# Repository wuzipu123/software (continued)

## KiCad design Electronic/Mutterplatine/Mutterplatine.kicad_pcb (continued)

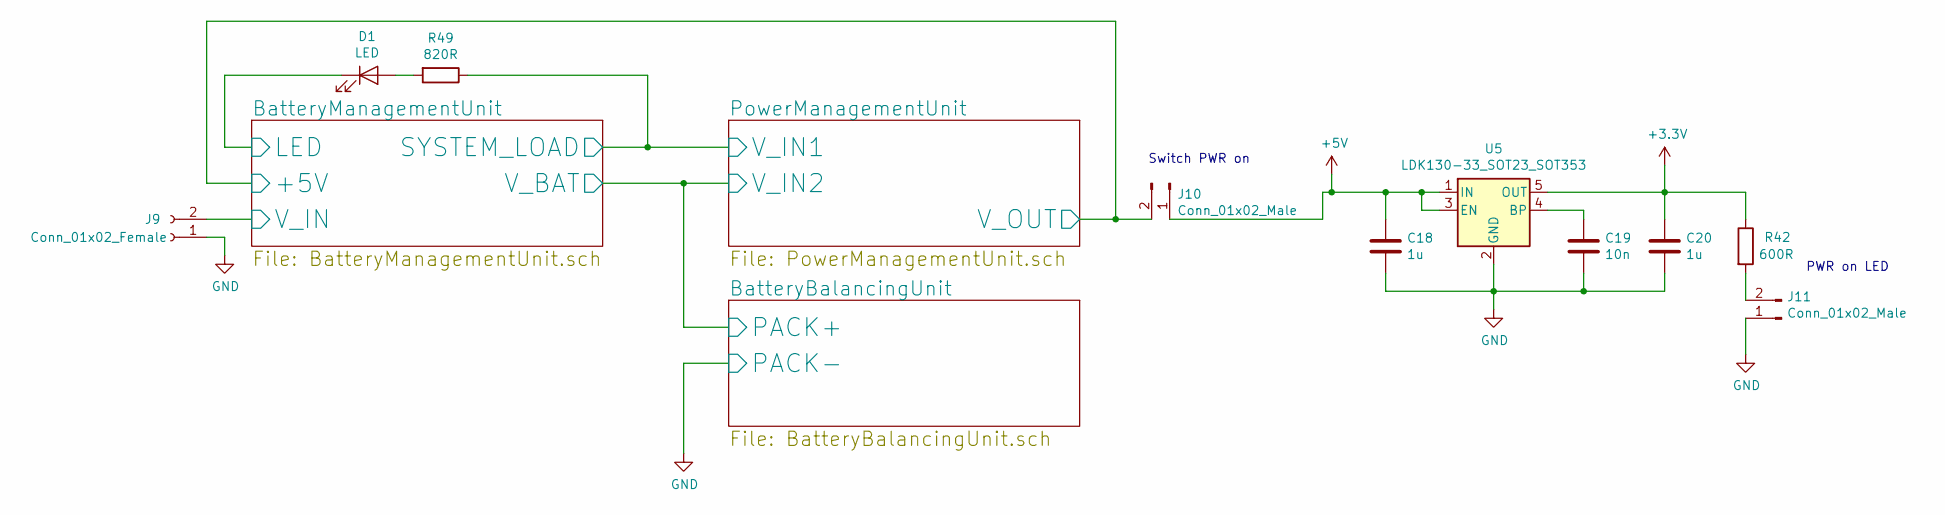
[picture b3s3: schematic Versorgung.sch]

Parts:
C18, C20: 1u; C_0805_2012Metric_Pad1.15x1.40mm_HandSolder
C19: 10n; C_0805_2012Metric_Pad1.15x1.40mm_HandSolder
D1: LED; Pin_Header_Straight_1x02_Pitch2.54mm
J9: Conn_01x02_Female; PhoenixContact_MCV-G_02x5.08mm_Vertical
J10, J11: Conn_01x02_Male; PinHeader_1x02_P2.54mm_Vertical
R42: 600R; R_0805_2012Metric_Pad1.15x1.40mm_HandSolder
R49: 820R; R_0805
U5: LDK130-33_SOT23_SOT353; SOT-23-5_HandSoldering

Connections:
+3V3: C20.2, R42.1, U5.5 (OUT); also elsewhere on the board
+5V: C18.2, J10.1, U5.1 (IN), U5.3 (EN); also elsewhere on the board
/Versorgung/BatteryManagementUnit/+5V: J10.2; also elsewhere on the board
/Versorgung/BatteryManagementUnit/LED: D1.1 (K); also elsewhere on the board
/Versorgung/BatteryManagementUnit/V_IN: J9.2; also elsewhere on the board
unnamed: C19.2, U5.4 (BP)
unnamed: D1.2 (A), R49.2
unnamed: J11.2, R42.2

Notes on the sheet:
PWR on LED
Switch PWR on

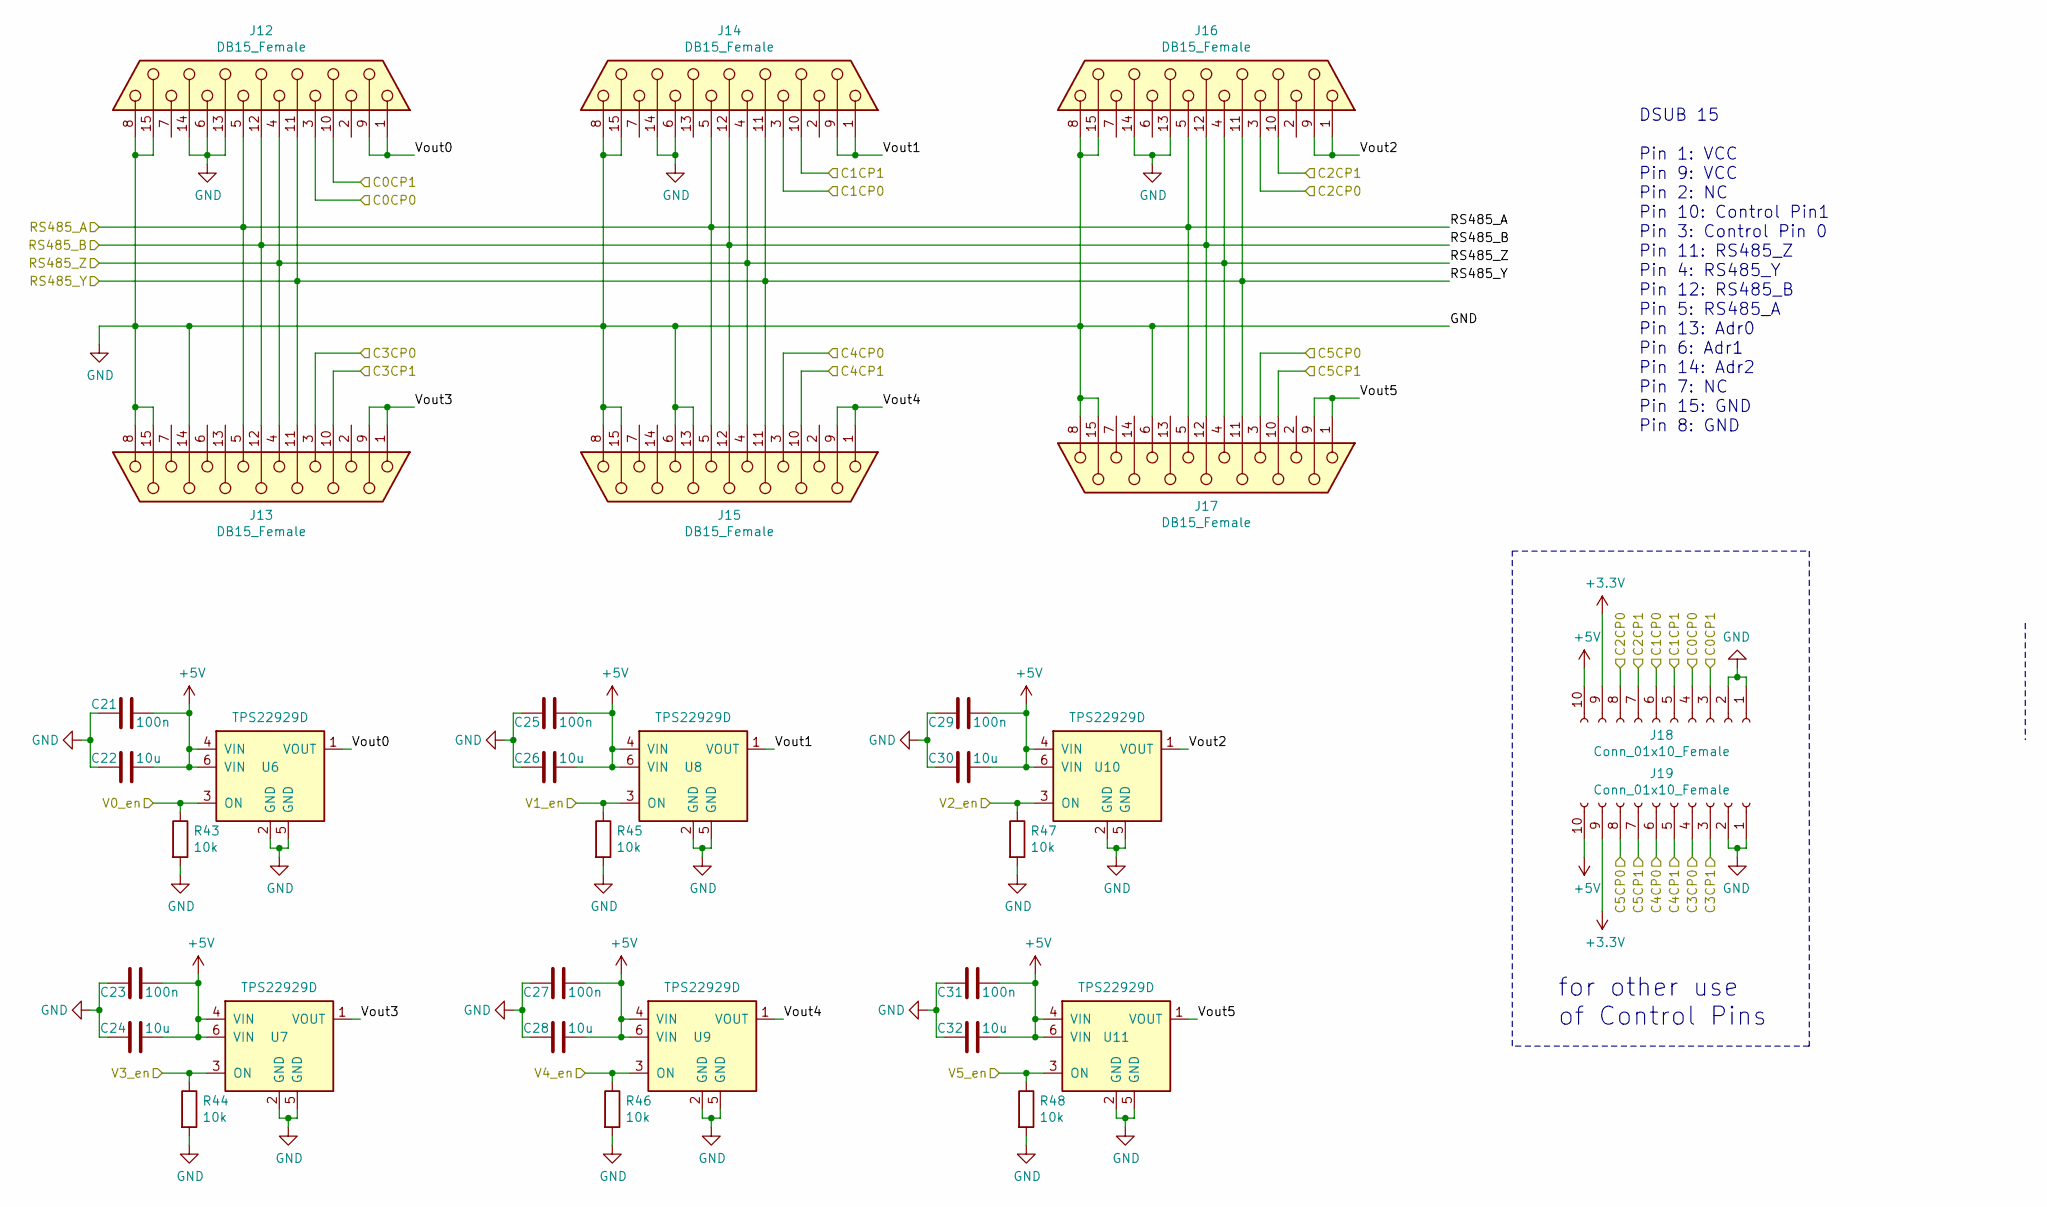
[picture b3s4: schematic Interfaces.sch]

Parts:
C21, C23, C25, C27, C29, C31: 100n; C_0805_2012Metric_Pad1.15x1.40mm_HandSolder
C22, C24, C26, C28, C30, C32: 10u; C_0805_2012Metric_Pad1.15x1.40mm_HandSolder
J12, J13, J14, J15, J16, J17: DB15_Female; DSUB-15_Female_Vertical_P2.77x2.84mm_MountingHoles
J18, J19: Conn_01x10_Female; PinSocket_1x10_P2.54mm_Vertical
R43, R44, R45, R46, R47, R48: 10k; R_0805_2012Metric_Pad1.15x1.40mm_HandSolder
U6, U7, U8, U9, U10, U11: TPS22929D; SOT-23-6

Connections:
+3V3: J18.9, J19.9; also elsewhere on the board
+5V: C21.2, C22.2, C23.2, C24.2, C25.2, C26.2, C27.2, C28.2, C29.2, C30.2, C31.2, C32.2, J18.10, J19.10, U6.4 (VIN), U6.6 (VIN), U7.4 (VIN), U7.6 (VIN), U8.4 (VIN), U8.6 (VIN), U9.4 (VIN), U9.6 (VIN), U10.4 (VIN), U10.6 (VIN), U11.4 (VIN), U11.6 (VIN); also elsewhere on the board
/C0CP0: J12.3, J18.4; also elsewhere on the board
/C0CP1: J12.10, J18.3; also elsewhere on the board
/C1CP1: J14.10, J18.5; also elsewhere on the board
/C2CP1: J16.10, J18.7; also elsewhere on the board
/C3CP0: J13.3, J19.4; also elsewhere on the board
/C3CP1: J13.10, J19.3; also elsewhere on the board
/C4CP0: J15.3, J19.6; also elsewhere on the board
/C4CP1: J15.10, J19.5; also elsewhere on the board
/C5CP0: J17.3, J19.8; also elsewhere on the board
/C5CP1: J17.10, J19.7; also elsewhere on the board
/Interfaces/Vout0: J12.1, J12.9, U6.1 (VOUT)
/Interfaces/Vout1: J14.1, J14.9, U8.1 (VOUT)
/Interfaces/Vout2: J16.1, J16.9, U10.1 (VOUT)
/Interfaces/Vout3: J13.1, J13.9, U7.1 (VOUT)
/Interfaces/Vout4: J15.1, J15.9, U9.1 (VOUT)
/Interfaces/Vout5: J17.1, J17.9, U11.1 (VOUT)
/RS485_A: J12.5, J13.5, J14.5, J15.5, J16.5, J17.5; also elsewhere on the board
/RS485_B: J12.12, J13.12, J14.12, J15.12, J16.12, J17.12; also elsewhere on the board
/RS485_Y: J12.11 (P111), J13.11 (P111), J14.11 (P111), J15.11 (P111), J16.11 (P111), J17.11 (P111); also elsewhere on the board
/RS485_Z: J12.4, J13.4, J14.4, J15.4, J16.4, J17.4; also elsewhere on the board
/V0_en: R43.1, U6.3 (ON); also elsewhere on the board
/V1_en: R45.1, U8.3 (ON); also elsewhere on the board
/V2_en: R47.1, U10.3 (ON); also elsewhere on the board
/V3_en: R44.1, U7.3 (ON); also elsewhere on the board
/V4_en: R46.1, U9.3 (ON); also elsewhere on the board
/V5_en: R48.1, U11.3 (ON); also elsewhere on the board

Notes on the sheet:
DSUB 15 Pin 1: VCC Pin 9: VCC Pin 2: NC Pin 10: Control Pin1 Pin 3: Control Pin 0 Pin 11: RS485_Z Pin 4: RS485_Y Pin 12: RS485_B Pin 5: RS485_A Pin 13: Adr0 Pin 6: Adr1 Pin 14: Adr2 Pin 7: NC Pin 15: GND Pin 8: GND
for other use of Control Pins

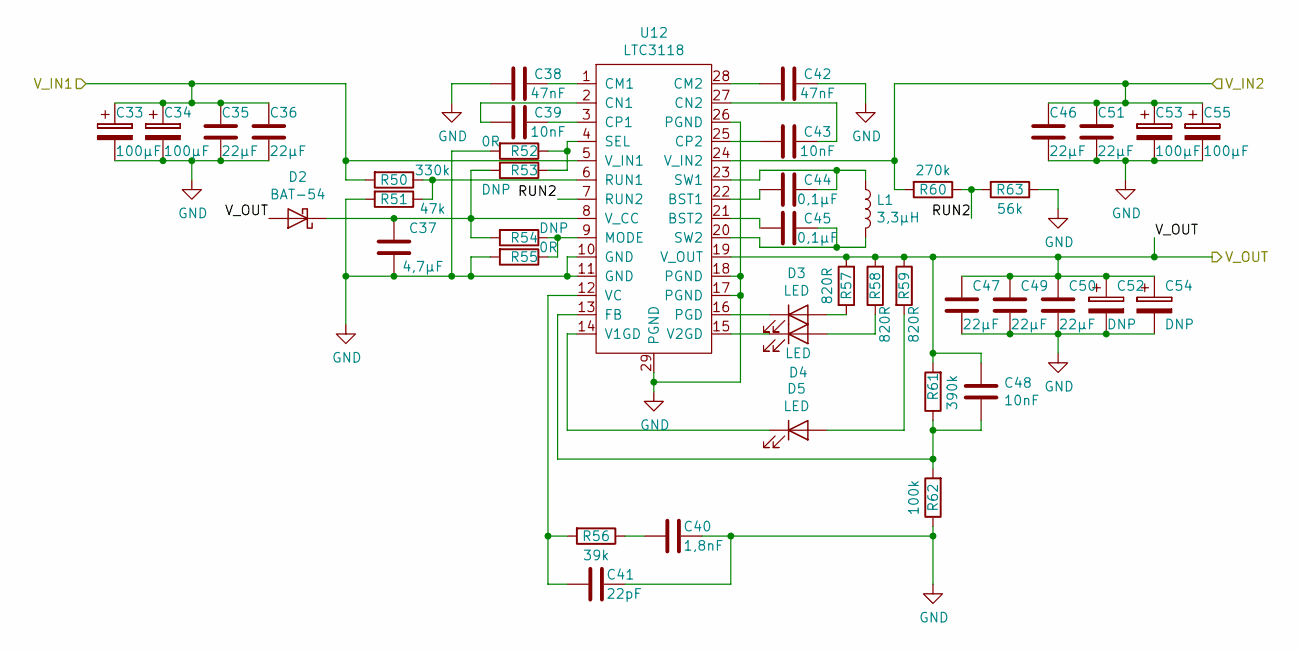
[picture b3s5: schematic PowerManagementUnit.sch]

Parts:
C33, C34, C53, C55: 100µF; CP_Tantalum_Case-X_EIA-7343-43_Wave
C35, C36, C46, C47, C49, C50, C51: 22µF; C_0805
C37: 4,7µF; C_0805
C38, C42: 47nF; C_0805
C39, C43, C48: 10nF; C_0805
C40: 1,8nF; C_0805
C41: 22pF; C_0805
C44, C45: 0,1µF; C_0805
C52, C54: DNP; CP_Tantalum_Case-D_EIA-7343-31_Wave
D2: BAT-54; D_SOT-23_ANK
D3, D4, D5: LED; LED_0603
L1: 3,3µH; L_Wuerth_WE-PD-6033_Handsoldering
R50: 330k; R_0805
R51: 47k; R_0805
R52, R55: 0R; R_0805
R53, R54: DNP; R_0805
R56: 39k; R_0805
R57, R58, R59: 820R; R_0805
R60: 270k; R_0805
R61: 390k; R_0805
R62: 100k; R_0805
R63: 56k; R_0805
U12: LTC3118; TSSOP-28-1EP_4.4x9.7mm_Pitch0.65mm

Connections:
/Versorgung/BatteryManagementUnit/+5V: C47.1, C48.1, C49.1, C50.1, C52.1, C54.1, D2.2 (A), R57.1, R58.2, R59.1, R61.2, U12.19 (V_OUT); also elsewhere on the board
/Versorgung/PowerManagementUnit/RUN2: R60.1, R63.2, U12.7 (RUN2)
unnamed: C37.2, D2.1 (K), R53.2, R54.2, U12.8 (V_CC)
unnamed: C38.1, U12.1 (CM1)
unnamed: C39.1, U12.3 (CP1)
unnamed: C39.2, U12.2 (CN1)
unnamed: C40.2, R56.1
unnamed: C41.2, R56.2, U12.12 (VC)
unnamed: C42.2, U12.28 (CM2)
unnamed: C43.1, U12.27 (CN2)
unnamed: C43.2, U12.25 (CP2)
unnamed: C44.1, U12.22 (BST1)
unnamed: C44.2, L1.1, U12.23 (SW1)
unnamed: C45.1, L1.2, U12.20 (SW2)
unnamed: C45.2, U12.21 (BST2)
unnamed: C48.2, R61.1, R62.2, U12.13 (FB)
unnamed 94: D3.1 (K), U12.16 (PGD); also elsewhere on the board
unnamed 95: D3.2 (A), R57.2; also elsewhere on the board
unnamed 96: D4.1 (K), U12.15 (V2GD); also elsewhere on the board
unnamed 97: D4.2 (A), R58.1; also elsewhere on the board
unnamed 98: D5.1 (K), U12.14 (V1GD); also elsewhere on the board
unnamed 99: D5.2 (A), R59.2; also elsewhere on the board
unnamed: R50.1, R51.1, U12.6 (RUN1)
unnamed: R52.1, R53.1, U12.4 (SEL)
unnamed: R54.1, R55.1, U12.9 (MODE)

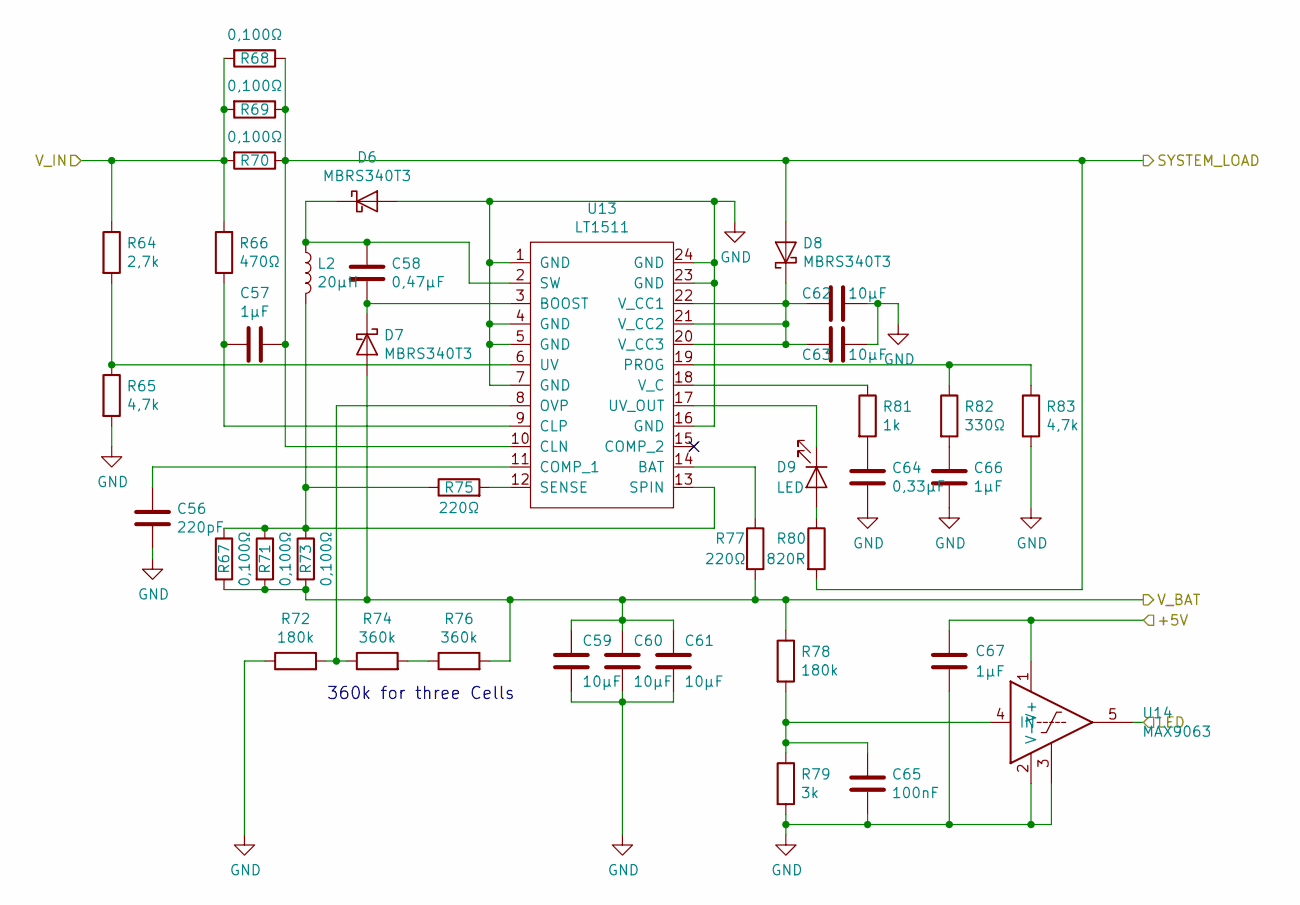
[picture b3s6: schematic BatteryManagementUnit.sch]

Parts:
C56: 220pF; C_0805
C57, C66: 1μF; C_0805
C58: 0,47μF; C_0805
C59, C60, C61: 10µF; C_0805
C62, C63: 10μF; C_0805
C64: 0,33μF; C_0805
C65: 100nF; C_0805
C67: 1µF; C_0805
D6, D7, D8: MBRS340T3; D_SMC
D9: LED; LED_0603
L2: 20μH; L_Wuerth_WE-PDF_Handsoldering
R7, R9: 360k; R_0805
R64: 2,7k; R_0805
R65, R83: 4,7k; R_0805
R66: 470Ω; R_0805
R67, R68, R69, R70, R71, R73: 0,100Ω; R_1206
R72, R78: 180k; R_0805
R75, R77: 220Ω; R_0805
R79: 3k; R_0805
R80: 820R; R_0805
R81: 1k; R_0805
R82: 330Ω; R_0805
U13: LT1511; TSOP-II-32_21.0x10.2mm_Pitch1.27mm
U14: MAX9063; SOT-23-5

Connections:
/Versorgung/BatteryManagementUnit/+5V: C67.2, U14.1 (V+); also elsewhere on the board
/Versorgung/BatteryManagementUnit/LED: U14.5; also elsewhere on the board
/Versorgung/BatteryManagementUnit/V_IN: R64.1, R66.2, R68.2, R69.2, R70.2; also elsewhere on the board
unnamed: C56.2, U13.11 (COMP_1)
unnamed: C57.1, R66.1, U13.9 (CLP)
unnamed: C58.1, D7.1 (K), U13.3 (BOOST)
unnamed: C58.2, D6.1 (K), L2.1, U13.2 (SW)
unnamed: C62.2, C63.2, D8.1 (K), U13.20 (V_CC3), U13.21 (V_CC2), U13.22 (V_CC1)
unnamed: C64.2, R81.2
unnamed: C65.1, R78.2, R79.1, U14.4 (IN)
unnamed: C66.2, R82.2
unnamed 100: D9.1 (K), U13.17 (UV_OUT); also elsewhere on the board
unnamed 101: D9.2 (A), R80.1; also elsewhere on the board
unnamed: L2.2, R67.1, R71.1, R73.1, R75.1, U13.13 (SPIN)
unnamed: R64.2, R65.1, U13.6 (UV)
unnamed: R75.2, U13.12 (SENSE)
unnamed: R77.1, U13.14 (BAT)
unnamed: R81.1, U13.18 (V_C)
unnamed: R82.1, R83.1, U13.19 (PROG)

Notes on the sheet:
360k for three Cells

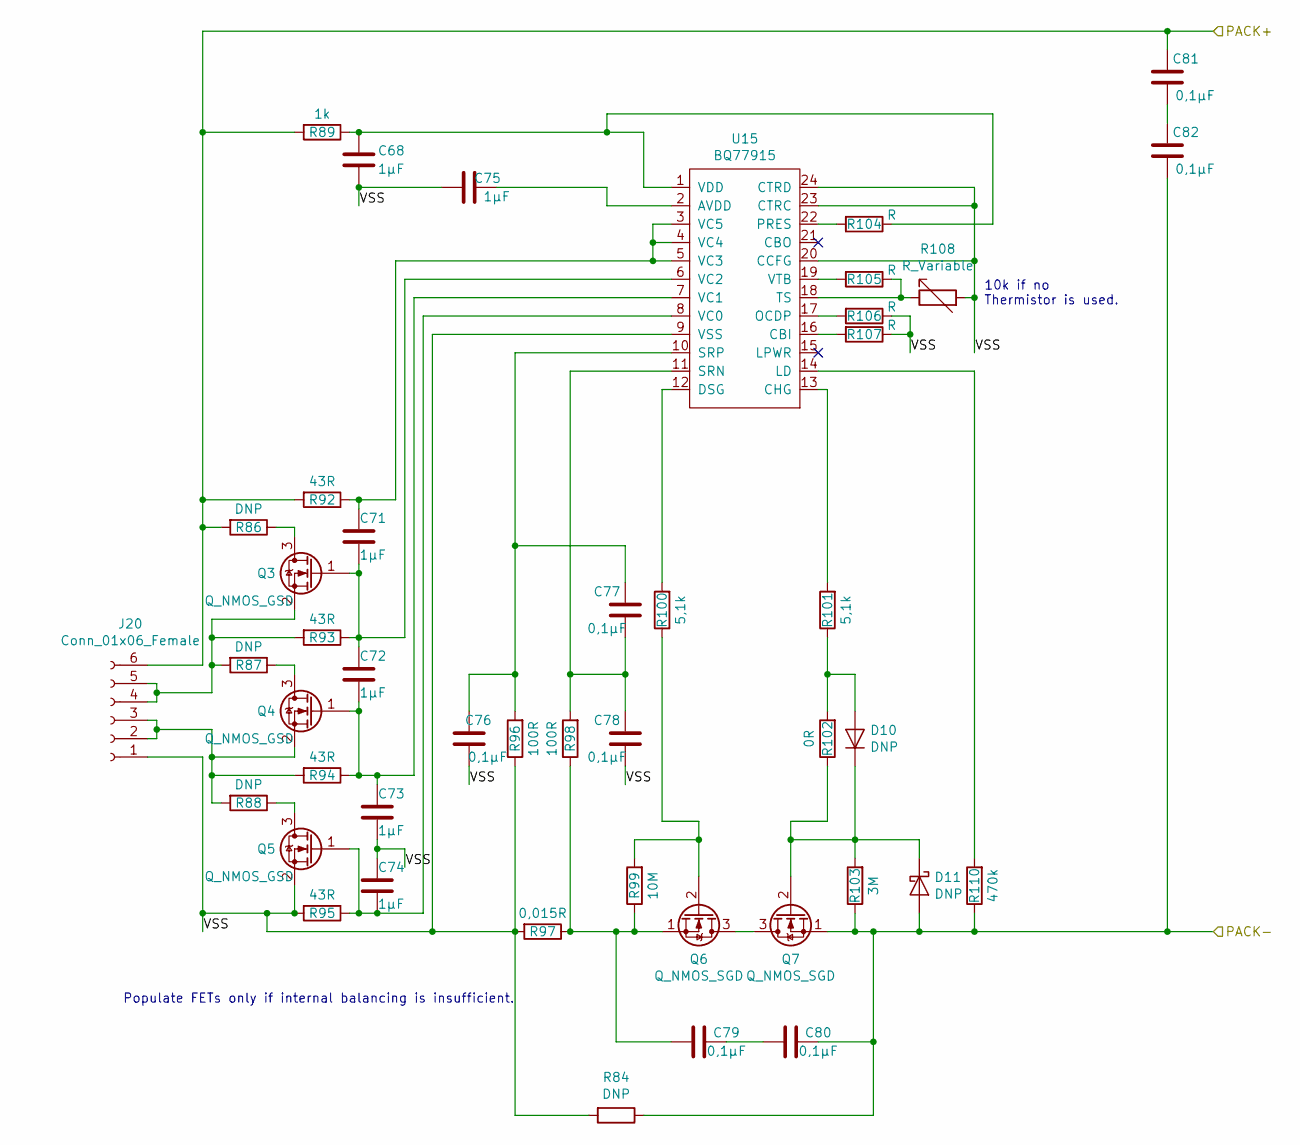
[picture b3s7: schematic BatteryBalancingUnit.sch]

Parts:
C4, C68, C72, C73, C74, C75: 1µF; C_0805
C76, C77, C78, C79, C80, C81, C82: 0,1µF; C_0805
D10, D11: DNP; D_0805
J20: Conn_01x06_Female; PhoenixContact_MCV-G_06x5.08mm_Vertical
Q3, Q4, Q5: Q_NMOS_GSD; TSOT-23
Q6, Q7: Q_NMOS_SGD; VSONP-8-1EP_5x6_Pitch1.27mm
R84: DNP; R_1206
R86, R87, R88: DNP; R_0805
R89: 1k; R_0805
R92, R93, R94, R95: 43R; R_0805
R96, R98: 100R; R_0805
R97: 0,015R; R_1206
R99: 10M; R_0805
R100, R101: 5,1k; R_0805
R102: 0R; R_0805
R103: 3M; R_0805
R104, R105, R106, R107: R; R_0805
R108: R_Variable; R_0805
R110: 470k; R_0805
U15: BQ77915; TSSOP-24_4.4x7.8mm_Pitch0.65mm

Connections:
/Versorgung/BatteryBalancingUnit/VSS: C68.1, C73.1, C74.2, C75.2, C76.1, C78.1, J20.1, Q5.2 (S), R84.2, R95.2, R96.1, R97.2, R106.1, R107.1, R108.2, U15.9 (VSS), U15.20 (CCFG), U15.23 (CTRC), U15.24 (CTRD)
unnamed: C68.2, R89.1, R104.1, U15.1 (VDD)
unnamed: C72.1, C73.2, Q4.1 (G), R94.1, U15.7 (VC1)
unnamed: C74.1, Q5.1 (G), R95.1, U15.8 (VC0)
unnamed: C75.1, U15.2 (AVDD)
unnamed: C76.2, C77.2, R96.2, U15.10 (SRP)
unnamed: C77.1, C78.2, R98.2, U15.11 (SRN)
unnamed: C79.1, C80.2
unnamed: C79.2, Q6.1 (S), R97.1, R98.1, R99.1
unnamed: C81.1, C82.2
unnamed: D10.1 (K), D11.1 (K), Q7.2 (G), R102.1, R103.2
unnamed: D10.2 (A), R101.1, R102.2
unnamed: J20.2, J20.3, Q4.2 (S), R88.2, R94.2
unnamed: J20.4, J20.5, Q3.2 (S), R87.2, R93.2
unnamed: Q3.3 (D), R86.1
unnamed: Q4.3 (D), R87.1
unnamed: Q5.3 (D), R88.1
unnamed: Q6.2 (G), R99.2, R100.1
unnamed: Q6.3 (D), Q7.3 (D)
unnamed: R100.2, U15.12 (DSG)
unnamed: R101.2, U15.13 (CHG)
unnamed: R104.2, U15.22 (PRES)
unnamed: R105.1, R108.1, U15.18 (TS)
unnamed: R105.2, U15.19 (VTB)
unnamed: R106.2, U15.17 (OCDP)
unnamed: R107.2, U15.16 (CBI)
unnamed: R110.2, U15.14 (LD)

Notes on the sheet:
Populate FETs only if internal balancing is insufficient.
10k if no Thermistor is used.

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
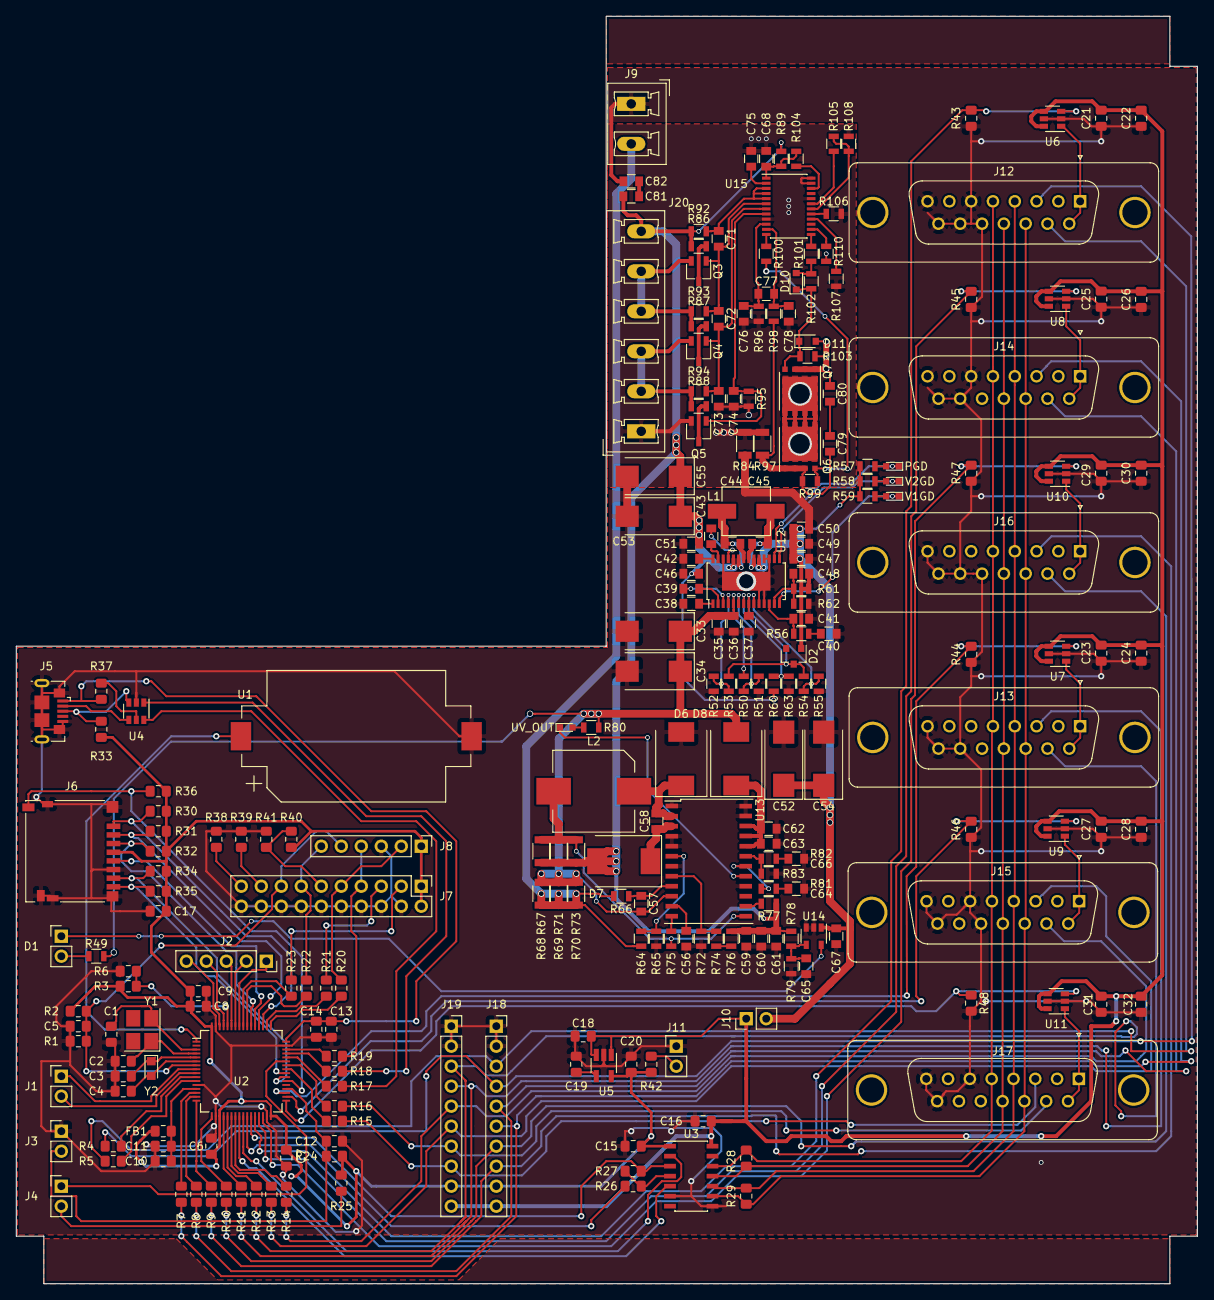
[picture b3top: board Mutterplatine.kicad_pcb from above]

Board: 2 copper layers, 150.0 x 161.0 mm, 242 parts (0 on the bottom side), 173 nets.

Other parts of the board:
C71: 1µF; C_0805
PGD: LED; LED_0603
R74, R76: 360k; R_0805
UV_OUT: LED; LED_0603
V1GD, V2GD: LED; LED_0603

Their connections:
unnamed 94: PGD.1; also elsewhere on the board
unnamed 95: PGD.2; also elsewhere on the board
unnamed 96: V2GD.1; also elsewhere on the board
unnamed 97: V2GD.2; also elsewhere on the board
unnamed 98: V1GD.1; also elsewhere on the board
unnamed 99: V1GD.2; also elsewhere on the board
unnamed 100: UV_OUT.1; also elsewhere on the board
unnamed 101: UV_OUT.2; also elsewhere on the board
unnamed: R74.2, R76.1

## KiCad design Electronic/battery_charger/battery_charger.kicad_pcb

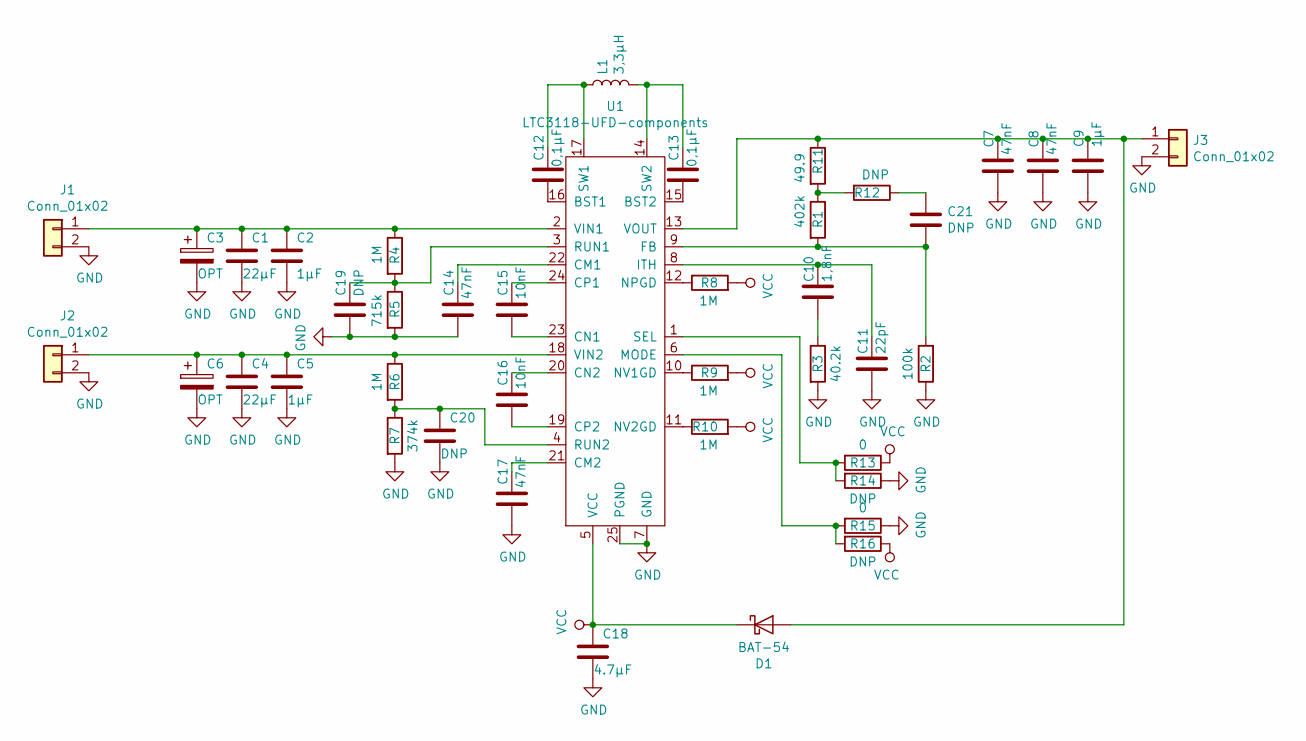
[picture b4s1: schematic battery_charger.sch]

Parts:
C1, C4: 22µF; C_1812_4532Metric
C2, C5, C9: 1µF; C_0603_1608Metric_Pad1.05x0.95mm_HandSolder
C3, C6: OPT; C_0603_1608Metric_Pad1.05x0.95mm_HandSolder
C7, C8: 47nF; C_1812_4532Metric
C10: 1,8nF; C_0603_1608Metric_Pad1.05x0.95mm_HandSolder
C11: 22pF; C_0603_1608Metric_Pad1.05x0.95mm_HandSolder
C12, C13: 0,1µF; C_0603_1608Metric_Pad1.05x0.95mm_HandSolder
C14, C17: 47nF; C_0603_1608Metric
C15, C16: 10nF; C_0603_1608Metric
C18: 4.7µF; C_0805_2012Metric_Pad1.15x1.40mm_HandSolder
C19, C20, C21: DNP; C_0603_1608Metric_Pad1.05x0.95mm_HandSolder
D1: BAT-54; D_SOD-523
J1, J2, J3: Conn_01x02; PinHeader_1x02_P2.54mm_Vertical
L1: 3,3µH; L_Wuerth_WE-PD-6033_Handsoldering
R1: 402k; R_0603_1608Metric
R2: 100k; R_0603_1608Metric
R3: 40.2k; R_0603_1608Metric
R4, R6, R8, R9, R10: 1M; R_0603_1608Metric
R5: 715k; R_0603_1608Metric
R7: 374k; R_0603_1608Metric
R11: 49.9; R_0603_1608Metric
R12, R14, R16: DNP; R_0603_1608Metric
R13, R15: 0; R_0603_1608Metric
U1: LTC3118-UFD-components; QFN-24-1EP_4x5mm_P0.5mm_EP2.65x3.65mm_ThermalVias

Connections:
GND: C1.2, C2.1, C3.2, C4.2, C5.2, C6.2, C7.2, C8.2, C9.2, C11.2, C14.2, C17.2, C18.2, C19.1, C20.2, J1.2, J2.2, J3.2, R2.1, R3.2, R5.2, R7.2, R14.1, R15.1, U1.7 (GND), U1.25 (PGND)
unnamed: C1.1, C2.2, C3.1, J1.1, R4.1, U1.2 (VIN1)
unnamed: C4.1, C5.1, C6.1, J2.1, R6.1, U1.18 (VIN2)
unnamed: C7.1, C8.1, C9.1, D1.2 (A), J3.1, R11.1, U1.13 (VOUT)
unnamed: C10.1, C11.1, U1.8 (ITH)
unnamed: C10.2, R3.1
unnamed: C12.1, U1.16 (BST1)
unnamed: C12.2, L1.1, U1.17 (SW1)
unnamed: C13.1, L1.2, U1.14 (SW2)
unnamed: C13.2, U1.15 (BST2)
unnamed: C14.1, U1.22 (CM1)
unnamed: C15.1, U1.24 (CP1)
unnamed: C15.2, U1.23 (CN1)
unnamed: C16.1, U1.20 (CN2)
unnamed: C16.2, U1.19 (CP2)
unnamed: C17.1, U1.21 (CM2)
unnamed: C19.2, R4.2, R5.1, U1.3 (RUN1)
unnamed: C20.1, R6.2, R7.1, U1.4 (RUN2)
unnamed: C21.1, R12.1
unnamed: C21.2, R1.2, R2.2, U1.9 (FB)
unnamed: R1.1, R11.2, R12.2
unnamed: R8.1, U1.12 (NPGD)
unnamed: R9.1, U1.10 (NV1GD)
unnamed: R10.1, U1.11 (NV2GD)
unnamed: R13.2, R14.2, U1.1 (SEL)
unnamed: R15.2, R16.2, U1.6 (MODE)
VCC: C18.1, D1.1 (K), R8.2, R9.2, R10.2, R13.1, R16.1, U1.5 (VCC)

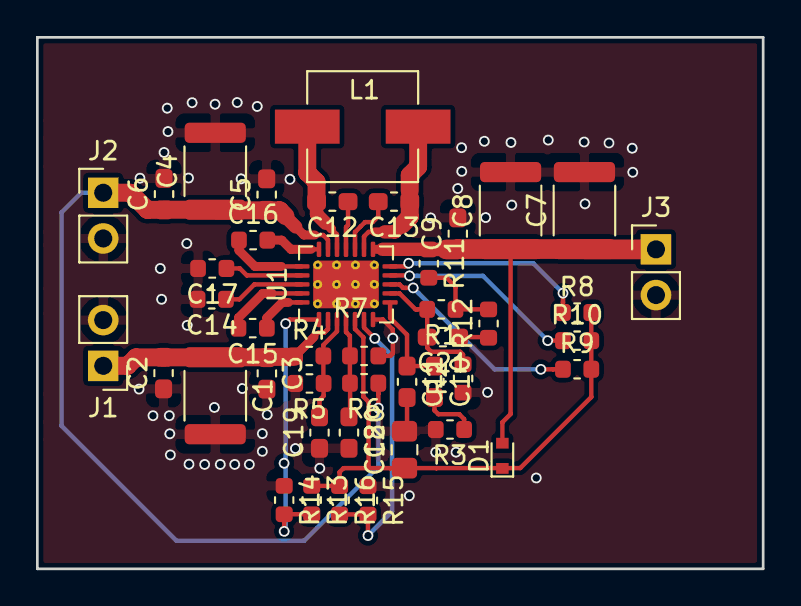
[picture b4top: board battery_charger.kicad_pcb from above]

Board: 2 copper layers, 40.3 x 29.5 mm, 43 parts (0 on the bottom side), 27 nets.

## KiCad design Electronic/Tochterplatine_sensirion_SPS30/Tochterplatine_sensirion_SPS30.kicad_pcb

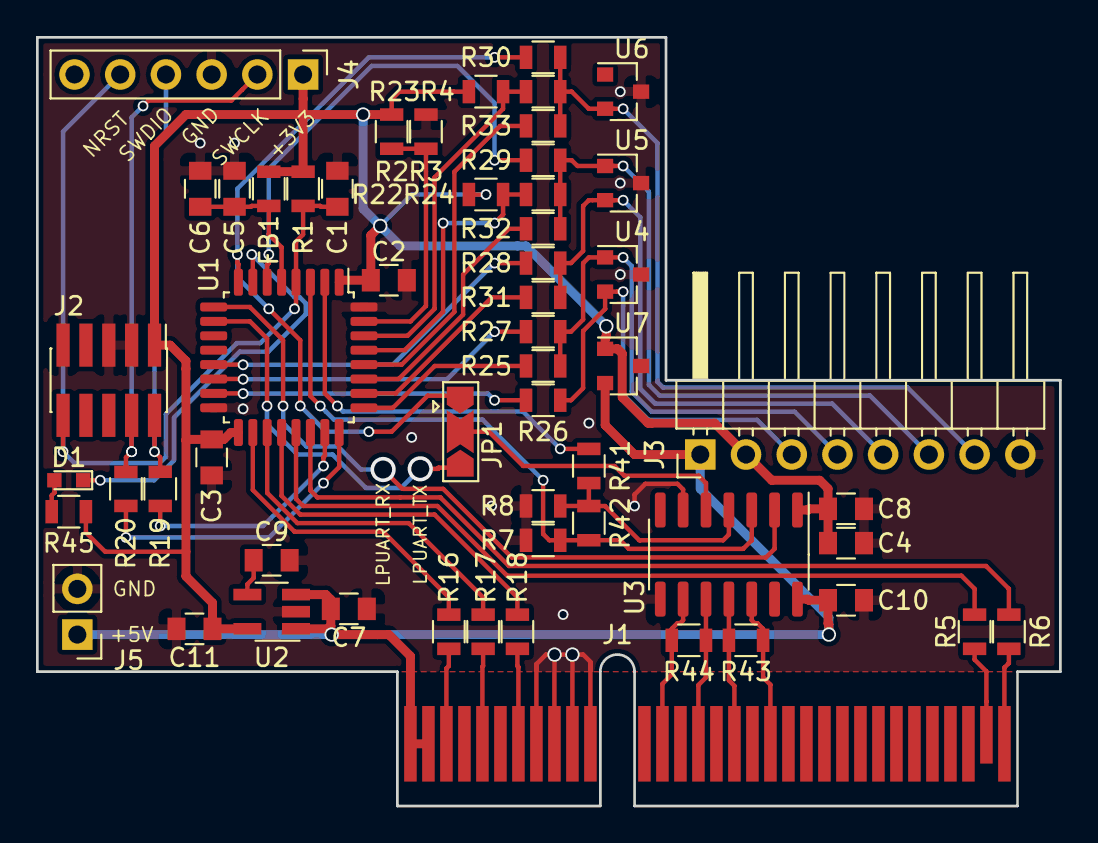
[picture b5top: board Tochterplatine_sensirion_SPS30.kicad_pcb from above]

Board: 2 copper layers, 56.8 x 42.7 mm, 56 parts (0 on the bottom side), 49 nets.

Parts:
C1, C2, C3, C5, C8, C10: 100n; C_0805
C4, C6, C7, C11: 1u; C_0805
C9: 10n; C_0805
D1: LED; LED_0603
FB1: Ferrite_Bead; L_0805
J1: PCIE-064-02-F-D-TH-tochter; SAMTEC_PCIE_064-02-F-D-TH-Tochter
J2: Conn_ARM_JTAG_SWD_10; PinHeader_2x05_P1.27mm_Vertical_SMD
J3: Conn_01x08_Male; PinHeader_1x08_P2.54mm_Horizontal
J4: Conn_01x06_Male; PinHeader_1x06_P2.54mm_Vertical
J5: Conn_01x02_Male; PinHeader_1x02_P2.54mm_Vertical
JP1: SolderJumper_3_Open; SolderJumper-3_P2.0mm_Open_TrianglePad1.0x1.5mm
R1, R2, R25, R26, R27, R28, R29, R30, R31, R32, R33, R41, R42: DNP; R_0805
R3, R7, R8: 10k; R_0805
R4, R5, R6, R19, R20, R24: 22R; R_0805
R16, R17, R18: 100R; R_0805
R22, R23: 4k7; R_0805
R43, R44: 120R; R_0805
R45: 480R; R_0805
U1: STM32L021K4Tx; LQFP-32_7x7mm_P0.8mm
U2: LDK130-33_SOT23_SOT353; SOT-23-5_HandSoldering
U3: MAX13432EESD; SOIC-14_3.9x8.7mm_P1.27mm
U4, U5, U6, U7: PESD2CAN; SOT-23

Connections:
+3V3: C2.1, C3.1, C4.1, C8.2, C11.2, FB1.1, J2.1, J3.2, J4.1, R1.1, R2.1, R22.1, R23.1, R45.1, U1.1, U1.17, U2.5, U3.1, U7.1
+5V: C7.2, C10.1, J1.B1, J1.B2, J3.1, J5.1, U2.1, U2.3, U3.14, U7.2
/Adr0: J1.B3, R16.1
/Adr1: J1.B5, R17.1
/Adr2: J1.B7, R18.1
/CP0: J1.B31, R5.2
/CP1: J1.B32, R6.2
/I2C_SCL: R22.2, R24.1, U1.29
/I2C_SDA: R4.1, R23.2, U1.30
/LPUART1_DE: R7.1, R42.1, U1.3, U3.3
/LPUART1_RE: R41.1, U1.2
/LPUART1_RX: U1.9, U3.2
/LPUART1_TX: JP1.2, U3.5
/LPUART1_TX_STM32L04: JP1.3, U1.10
/Main_Connection/RS485_A: J1.B19, R43.1, U3.12
/Main_Connection/RS485_B: J1.B17, R43.2, U3.11
/Main_Connection/RS485_Y: J1.B13, R44.1, U3.9
/Main_Connection/RS485_Z: J1.B15, R44.2, U3.10
/NRST: C1.1, J2.10, J4.5, R1.2, U1.4
/SPI_MISO: R32.1, U1.27
/SPI_MOSI: R33.1, U1.28
/SPI_NSS: R25.1, U1.25
/SPI_SCK: R31.1, U1.26
/SWCLK: J2.4, J4.2, R20.1
/SWDIO: J2.2, J4.4, R19.1
/USART2_CK: R26.1, U1.15
/USART2_CTS: R28.1, U1.13
/USART2_RTS_DE: R27.1, U1.14
/USART2_RX: R29.1, U1.6
/USART2_TX_STM32L051: JP1.1, R30.1, U1.8
GND: C1.2, C2.2, C3.2, C4.2, C5.2, C6.2, C7.1, C8.1, C9.1, C10.2, C11.1, J1.B8, J1.B9, J1.B10, J1.B11, J2.3, J2.5, J2.9, J3.8, J4.3, J5.2, R3.2, R7.2, R8.2, U1.16, U1.32, U2.2, U3.6, U3.8, U4.3, U5.3, U6.3, U7.3
unnamed: C5.1, C6.1, FB1.2, U1.5
unnamed: C9.2, U2.4
unnamed: D1.1, U1.7
unnamed: D1.2, R45.2
unnamed: J3.3, R26.2, U4.2
unnamed: J3.4, R25.2, R27.2, U4.1
unnamed: J3.5, R28.2, R31.2, U5.2
unnamed: J3.6, R24.2, R29.2, R32.2, U5.1
unnamed: J3.7, R4.2, R30.2, R33.2, U6.2
unnamed: R2.2, R3.1, U1.31
unnamed: R5.1, U1.21
unnamed: R6.1, U1.22
unnamed: R16.2, U1.18
unnamed: R17.2, U1.19
unnamed: R18.2, U1.20
unnamed: R19.2, U1.23
unnamed: R20.2, U1.24
unnamed: R8.1, R41.2, R42.2, U3.4
